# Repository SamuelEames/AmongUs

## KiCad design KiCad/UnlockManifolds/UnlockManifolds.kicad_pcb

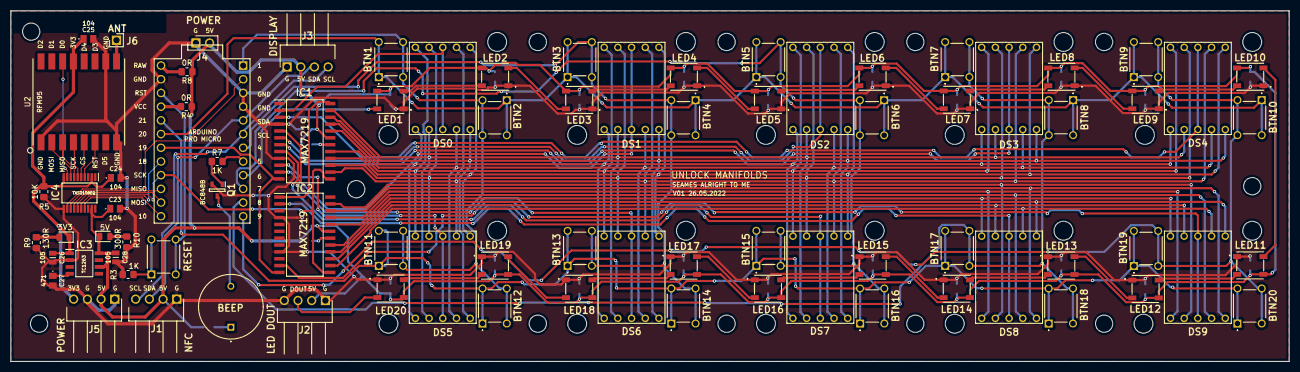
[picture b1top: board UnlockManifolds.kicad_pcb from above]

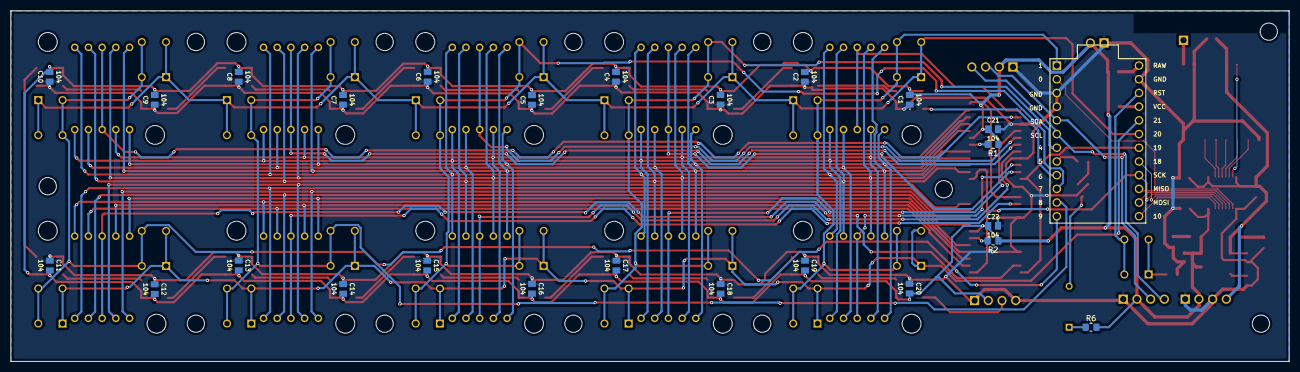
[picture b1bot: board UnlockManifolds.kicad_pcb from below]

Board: 4 copper layers, 237.0 x 65.0 mm, 105 parts (26 on the bottom side), 87 nets.

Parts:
3V3, 5V: LED; LED_0805_2012Metric
BTN1, BTN2, BTN3, BTN4, BTN5, BTN6, BTN7, BTN8, BTN9, BTN10, BTN11, BTN12, BTN13, BTN14, BTN15, BTN16, BTN17, BTN18, BTN19, BTN20: -; TS026660BK100LCRD
C1, C2, C3, C4, C5, C6, C7, C8, C9, C10, C11, C12, C13, C14, C15, C16, C17, C18, C19, C20, C21, C22, C23, C24, C25: 104; C0805
C26, C28: 105; CAPC2012X135N
C27: 471; C0805
DS0, DS1, DS2, DS3, DS4, DS5, DS6, DS7, DS8, DS9: HDSP-511A; HDSP511A
IC1, IC2: MAX7219; SOIC127P1032X265-24N
IC3: TC1263; SOIC127P600X175-8N
IC4: TXS0108EQ; SOP65P640X120-20N
J1: NFC; HDRRA4W67P0X254_1X4_1016X254X241P
J2: LED DOUT; HDRRA4W67P0X254_1X4_1016X254X241P
J3: DISPLAY; HDRRA4W67P0X254_1X4_1016X254X241P
J4: POWER; HDRV2W66P0X254_1X2_508X254X874P
J5: POWER; HDRRA4W67P0X254_1X4_1016X254X241P
J6: ANT; HDRV1W67P0X254_1X1_254X241X1082P
LED1, LED2, LED3, LED4, LED5, LED6, LED7, LED8, LED9, LED10, LED11, LED12, LED13, LED14, LED15, LED16, LED17, LED18, LED19, LED20: -; WS2812BB
LS1: BEEP; CMI12950585T
Q1: BC848B; SOT95P230X110-3N
R1, R2: R; R_0805_2012Metric_Pad1.20x1.40mm_HandSolder
R3, R6, R7: 1K; R_0805_2012Metric_Pad1.20x1.40mm_HandSolder
R4, R8: 0R; R_0805_2012Metric_Pad1.20x1.40mm_HandSolder
R5: 10K; R_0805_2012Metric_Pad1.20x1.40mm_HandSolder
R9: 130R; R_0805_2012Metric_Pad1.20x1.40mm_HandSolder
R10: 300R; R_0805_2012Metric_Pad1.20x1.40mm_HandSolder
RESET: -; TS026660BK100LCRD
U1: ProMicro
U2: RFM9X-S; RFM9X-SMD

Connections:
+3V3: 3V3.1, C24.1, C25.1, C26.1, IC3.1, IC4.2, IC4.10, J5.4, R5.1, U2.13
+5V: 5V.1, C1.2, C2.2, C3.2, C4.2, C5.2, C6.2, C7.2, C8.2, C9.2, C10.2, C11.2, C12.2, C13.2, C14.2, C15.2, C16.2, C17.2, C18.2, C19.2, C20.2, C21.1, C22.1, C23.1, C28.1, IC1.19, IC2.19, IC3.6, IC3.8, IC4.19, J1.2, J2.2, J3.2, J4.2, J5.2, LED1.3, LED2.3, LED3.3, LED4.3, LED5.3, LED6.3, LED7.3, LED8.3, LED9.3, LED10.3, LED11.3, LED12.3, LED13.3, LED14.3, LED15.3, LED16.3, LED17.3, LED18.3, LED19.3, LED20.3, R1.1, R2.1, R4.1, R6.2, R8.1
/BEEP: R7.2, U1.8
/BMTX_C0: BTN1.3, BTN1.4, BTN2.3, BTN2.4, BTN11.3, BTN11.4, BTN12.3, BTN12.4, U1.1
/BMTX_C1: BTN3.3, BTN3.4, BTN4.3, BTN4.4, BTN13.3, BTN13.4, BTN14.3, BTN14.4, U1.7
/BMTX_C2: BTN5.3, BTN5.4, BTN6.3, BTN6.4, BTN15.3, BTN15.4, BTN16.3, BTN16.4, U1.10
/BMTX_C3: BTN7.3, BTN7.4, BTN8.3, BTN8.4, BTN17.3, BTN17.4, BTN18.3, BTN18.4, U1.11
/BMTX_C4: BTN9.3, BTN9.4, BTN10.3, BTN10.4, BTN19.3, BTN19.4, BTN20.3, BTN20.4, U1.12
/BMTX_R0: BTN1.1, BTN1.2, BTN2.1, BTN2.2, BTN3.1, BTN3.2, BTN4.1, BTN4.2, BTN5.1, BTN5.2, BTN6.1, BTN6.2, BTN7.1, BTN7.2, BTN8.1, BTN8.2, BTN9.1, BTN9.2, BTN10.1, BTN10.2, U1.19
/BMTX_R1: BTN11.1, BTN11.2, BTN12.1, BTN12.2, BTN13.1, BTN13.2, BTN14.1, BTN14.2, BTN15.1, BTN15.2, BTN16.1, BTN16.2, BTN17.1, BTN17.2, BTN18.1, BTN18.2, BTN19.1, BTN19.2, BTN20.1, BTN20.2, U1.20
/DISP_CS: IC1.12, IC2.12, U1.18
/LED_DIN: LED1.4, U1.9
/LED_DOUT: J2.3, LED20.2
/MISO: IC4.13, U1.15
/MOSI: IC4.14, U1.14
/RST: RESET.3, RESET.4, U1.22
/SCK: IC1.13, IC2.13, IC4.15, U1.16
/SCL: J1.4, J3.4, U1.6
/SDA: J1.3, J3.3, U1.5
GND: C1.1, C2.1, C3.1, C4.1, C5.1, C6.1, C7.1, C8.1, C9.1, C10.1, C11.1, C12.1, C13.1, C14.1, C15.1, C16.1, C17.1, C18.1, C19.1, C20.1, C21.2, C22.2, C23.2, C24.2, C25.2, C26.2, C27.2, C28.2, IC1.4, IC1.9, IC2.4, IC2.9, IC3.2, IC4.11, J1.1, J2.1, J2.4, J3.1, J4.1, J5.1, J5.3, LED1.1, LED2.1, LED3.1, LED4.1, LED5.1, LED6.1, LED7.1, LED8.1, LED9.1, LED10.1, LED11.1, LED12.1, LED13.1, LED14.1, LED15.1, LED16.1, LED17.1, LED18.1, LED19.1, LED20.1, Q1.2, R3.1, R5.2, R9.1, R10.1, U1.3, U1.4, U1.23, U2.1, U2.8, U2.10
unnamed: 3V3.2, R9.2
unnamed: 5V.2, R10.2
unnamed: C27.1, IC3.4
unnamed: DS0.1, DS1.1, DS2.1, DS3.1, DS4.1, DS5.1, DS6.1, DS7.1, IC1.21
unnamed: DS0.2, DS1.2, DS2.2, DS3.2, DS4.2, DS5.2, DS6.2, DS7.2, IC1.23
unnamed: DS0.3, DS0.8, IC1.2
unnamed: DS0.4, DS1.4, DS2.4, DS3.4, DS4.4, DS5.4, DS6.4, DS7.4, IC1.20
unnamed: DS0.5, DS1.5, DS2.5, DS3.5, DS4.5, DS5.5, DS6.5, DS7.5, IC1.22
unnamed: DS0.6, DS1.6, DS2.6, DS3.6, DS4.6, DS5.6, DS6.6, DS7.6, IC1.16
unnamed: DS0.7, DS1.7, DS2.7, DS3.7, DS4.7, DS5.7, DS6.7, DS7.7, IC1.14
unnamed: DS0.9, DS1.9, DS2.9, DS3.9, DS4.9, DS5.9, DS6.9, DS7.9, IC1.15
unnamed: DS0.10, DS1.10, DS2.10, DS3.10, DS4.10, DS5.10, DS6.10, DS7.10, IC1.17
unnamed: DS1.3, DS1.8, IC1.11
unnamed: DS2.3, DS2.8, IC1.6
unnamed: DS3.3, DS3.8, IC1.7
unnamed: DS4.3, DS4.8, IC1.3
unnamed: DS5.3, DS5.8, IC1.10
unnamed: DS6.3, DS6.8, IC1.5
unnamed: DS7.3, DS7.8, IC1.8
unnamed: DS8.1, DS9.1, IC2.21
unnamed: DS8.2, DS9.2, IC2.23
unnamed: DS8.3, DS8.8, IC2.2
unnamed: DS8.4, DS9.4, IC2.20
unnamed: DS8.5, DS9.5, IC2.22
unnamed: DS8.6, DS9.6, IC2.16
unnamed: DS8.7, DS9.7, IC2.14
unnamed: DS8.9, DS9.9, IC2.15
unnamed: DS8.10, DS9.10, IC2.17
unnamed: DS9.3, DS9.8, IC2.11
unnamed: IC1.18, R1.2
unnamed: IC1.24, IC2.1
unnamed: IC2.18, R2.2
unnamed: IC4.4, U2.6
unnamed: IC4.5, U2.5
unnamed: IC4.6, U2.4
unnamed: IC4.7, U2.3
unnamed: IC4.8, U2.2
unnamed: IC4.9, U2.14
unnamed: IC4.12, U1.2
unnamed: IC4.16, U1.17
unnamed: IC4.17, U1.13
unnamed: J6.1, U2.9
unnamed: LED1.2, LED2.4
unnamed: LED2.2, LED3.4
unnamed: LED3.2, LED4.4
unnamed: LED4.2, LED5.4
unnamed: LED5.2, LED6.4
unnamed: LED6.2, LED7.4
unnamed: LED7.2, LED8.4
unnamed: LED8.2, LED9.4
unnamed: LED10.2, LED11.4
unnamed: LED9.2, LED10.4
unnamed: LED11.2, LED12.4
unnamed: LED12.2, LED13.4
unnamed: LED13.2, LED14.4
unnamed: LED14.2, LED15.4
unnamed: LED15.2, LED16.4
unnamed: LED16.2, LED17.4
unnamed: LED17.2, LED18.4
unnamed: LED18.2, LED19.4
unnamed: LED19.2, LED20.4
unnamed: LS1.1, R6.1
unnamed: LS1.2, Q1.3
unnamed: Q1.1, R7.1
unnamed: R3.2, RESET.1, RESET.2
unnamed: R4.2, U1.21
unnamed: R8.2, U1.24

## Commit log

2022-09-24 Some additions
2022-09-24 Some more additions
2022-09-24 Added genSeq and write7seg functions
2022-09-25 Displays numbers and lights button LEDs
2022-09-25 Correct/Incorrect LEDs accodring to button seq
2022-09-26 Added some animations for start/end of game
2022-09-26 Tidied Code. Added gameRunning variable
